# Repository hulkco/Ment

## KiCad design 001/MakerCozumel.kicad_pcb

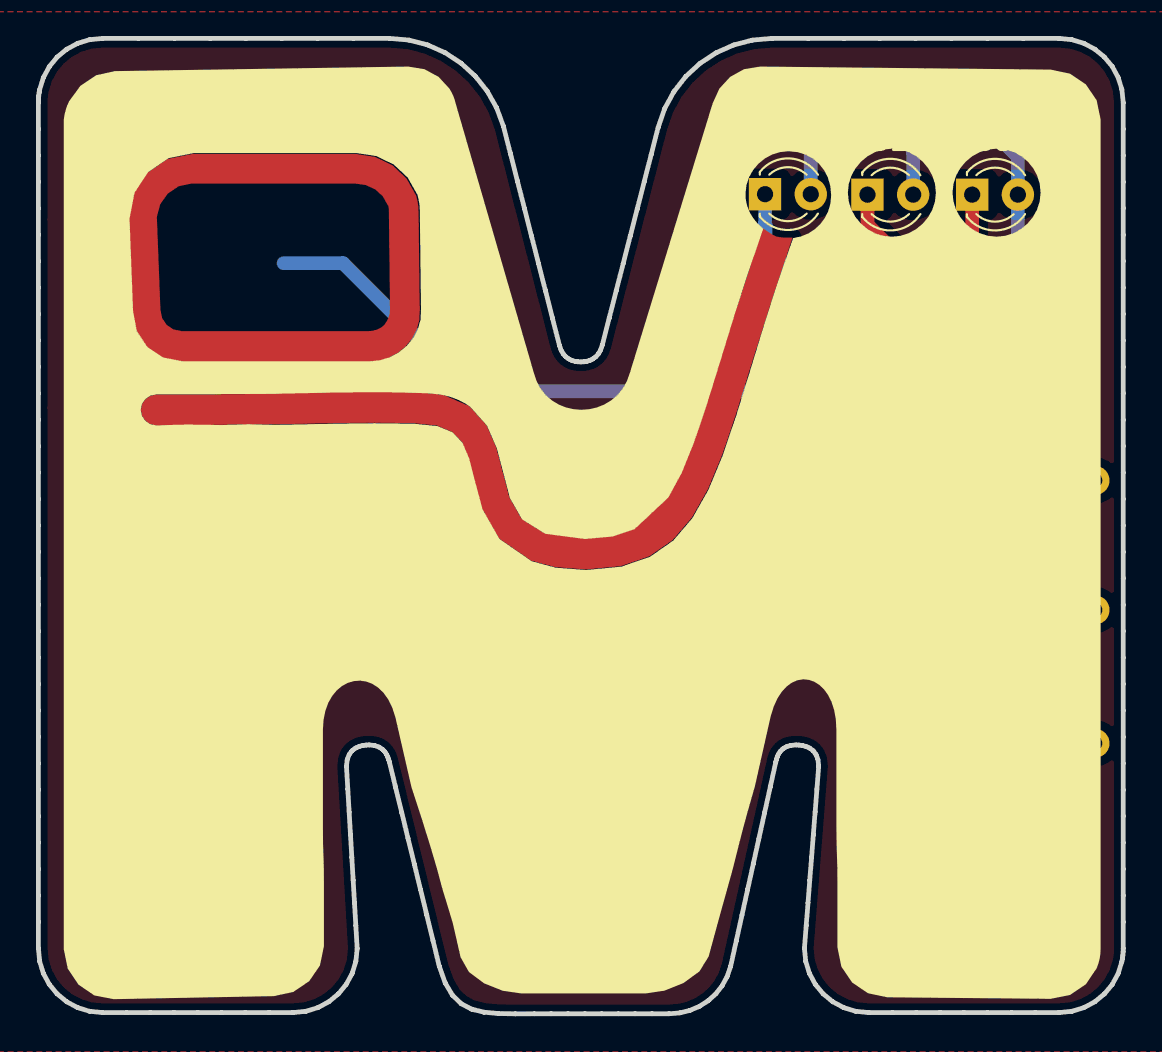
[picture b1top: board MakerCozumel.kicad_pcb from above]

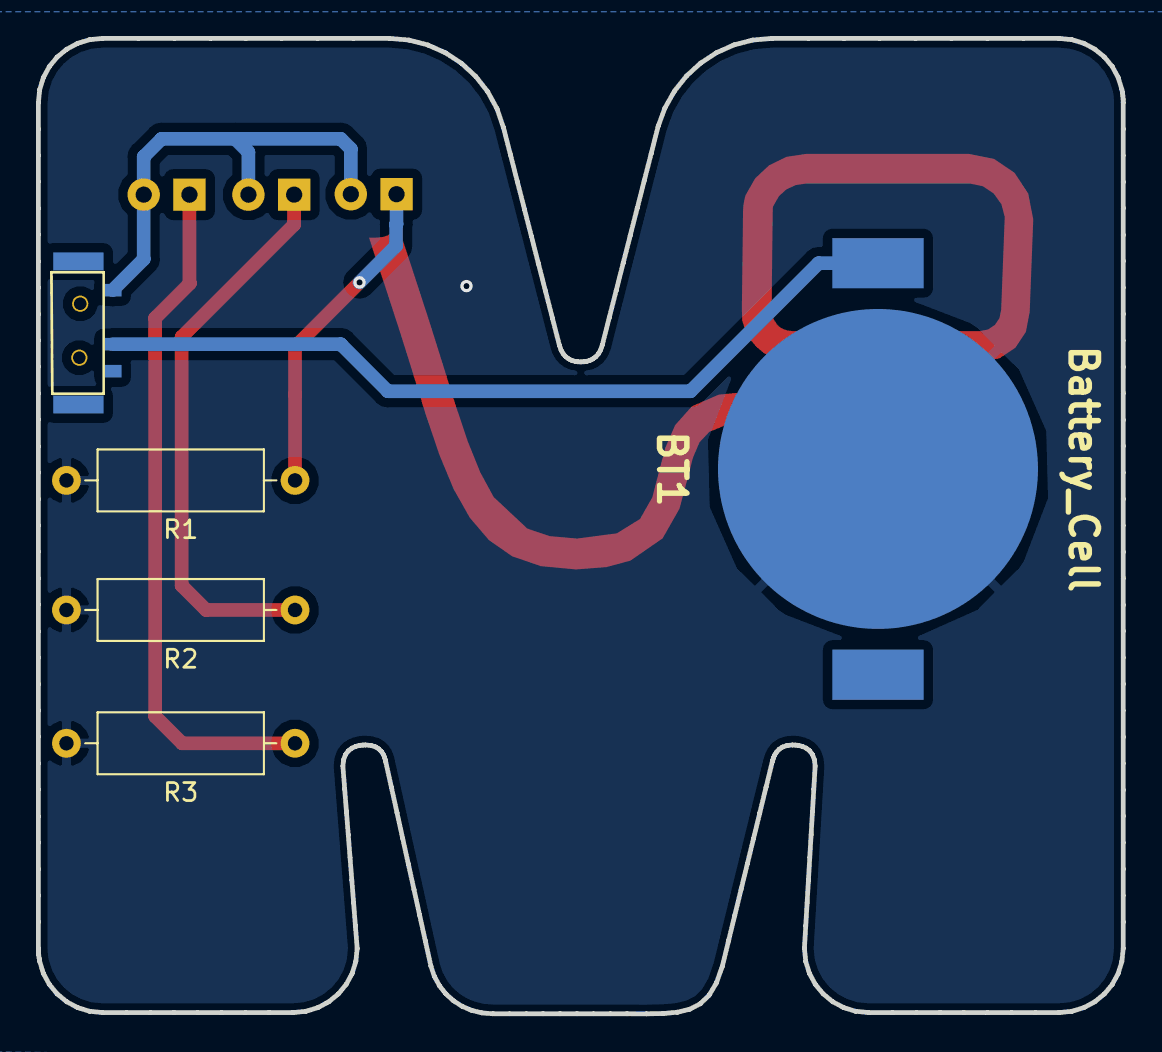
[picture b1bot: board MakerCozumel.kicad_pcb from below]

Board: 2 copper layers, 60.3 x 54.2 mm, 9 parts (5 on the bottom side), 6 nets.

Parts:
BT1: Battery_Cell; CR2032_MPD_BK912_SMT
D1, D2, D3: LED; LED_D3.0mm
P1: Edge; Ment.All.01
R1, R2, R3: R; R_Axial_DIN0309_L9.0mm_D3.2mm_P12.70mm_Horizontal
SW1: SW_SPDT; MSK12C02

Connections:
GND: BT1.2, R1.2, R2.2, R3.2
unnamed: BT1.1, SW1.2
unnamed: D1.1, R1.1
unnamed: D1.2, D2.2, D3.2, SW1.1
unnamed: D2.1, R2.1
unnamed: D3.1, R3.1

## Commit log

2018-11-14 Firts Upload
2018-11-15 Update 15 Nov 2018
2019-01-10 Some updates
